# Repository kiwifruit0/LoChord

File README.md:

# LoChord

A real-time MIDI chord controller for **ESP32-P4**, with chord generation, looping, and parameter control. Inspired by the [HiChord](https://hichord.shop/), but not a clone — see `CLAUDE.md` for how the two differ.

LoChord is both a firmware project and a hardware project developed together in one repo.

> **Mid-migration.** The project moved from the ESP32-S3-WROOM-1 to the WT0132P4-A1 (ESP32-P4) module during design. `PINOUT.md` is written against the P4; `firmware/include/config.h` and the KiCad schematic are not yet. See `PINOUT.md`'s "Migration delta" for the work list, and the root `CLAUDE.md` for why the move was made.

## Hardware at a glance

- **WT0132P4-A1-N16R32** module — ESP32-P4, dual-core RISC-V, 16MB flash, 32MB in-package PSRAM, no radio
- 7× Kailh Choc v1 chord switches + 1× loop button, hand-soldered, direct GPIO
- 3× ALPS EC11 clickable rotary encoders (1 UI, 2 control)
- Nintendo Switch joystick module on a 5-pin FPC
- 428×142 2.79" NV3007 TFT LCD, SPI, LVGL UI built in EEZ Studio
- **ES8388** stereo I2S codec with integrated headphone amp, driving a 3.5mm jack
- Native USB, **MIDI only** — recording is via the headphone jack into an audio interface
- 4-pin USB-Serial-JTAG debug header (works concurrently with USB MIDI)

## Repository layout

```
/
├── firmware/     ESP32-P4 PlatformIO project (Arduino framework, via pioarduino)
├── lochord_hw/   KiCad hardware project (schematic + PCB)
└── PINOUT.md     Single source of truth for every pin/net crossing the firmware↔hardware boundary
```

Each directory has its own `CLAUDE.md` with more detail; start with the root `CLAUDE.md` for the full picture.

## Firmware

Built against **`pioarduino/platform-espressif32`**, not the official `platformio/espressif32` platform. The official platform never picked up Arduino-ESP32 3.x (needed for USB MIDI) and has no ESP32-P4 support.

A **custom board JSON is required** — no stock definition matches the N16R32 (16MB flash / 32MB PSRAM) module.

### Development commands

Run from `firmware/`:

Generate `compile_commands.json`:
```
pio run -t compiledb
```

Build and upload:
```
pio run -t upload
```

Serial monitor:
```
pio device monitor
```
Exit with `Ctrl+A` then `Ctrl+X`

Host tests:
```
pio test -e native
```

## Hardware

The schematic (`lochord_hw.kicad_sch`) and PCB (`lochord_hw.kicad_pcb`) live in `lochord_hw/`. After a fresh clone, run:
```
git submodule update --init
```
to pull in the Kailh switch footprint library — without it, KiCad can't resolve the switch footprints.

Note that the switches are **Choc v1** (`PG1350`). Any Choc v2 footprint still present in the schematic is left over from an earlier revision and is wrong.

## Commit convention

Commits are prefixed by which side of the repo they touch:

- `fw:` — firmware-only changes
- `hw:` — hardware-only changes (including schematic/PCB edits)
- `chore:` — repo-wide changes that aren't feature work on either side (restructuring, docs, tooling)
- `fw+hw:` — changes that necessarily touch both sides together (e.g. reassigning a pin)

e.g. `fw: add strum direction toggle`, `hw: swap choc v2 footprints for v1`, `fw+hw: renumber gpio for esp32-p4`.

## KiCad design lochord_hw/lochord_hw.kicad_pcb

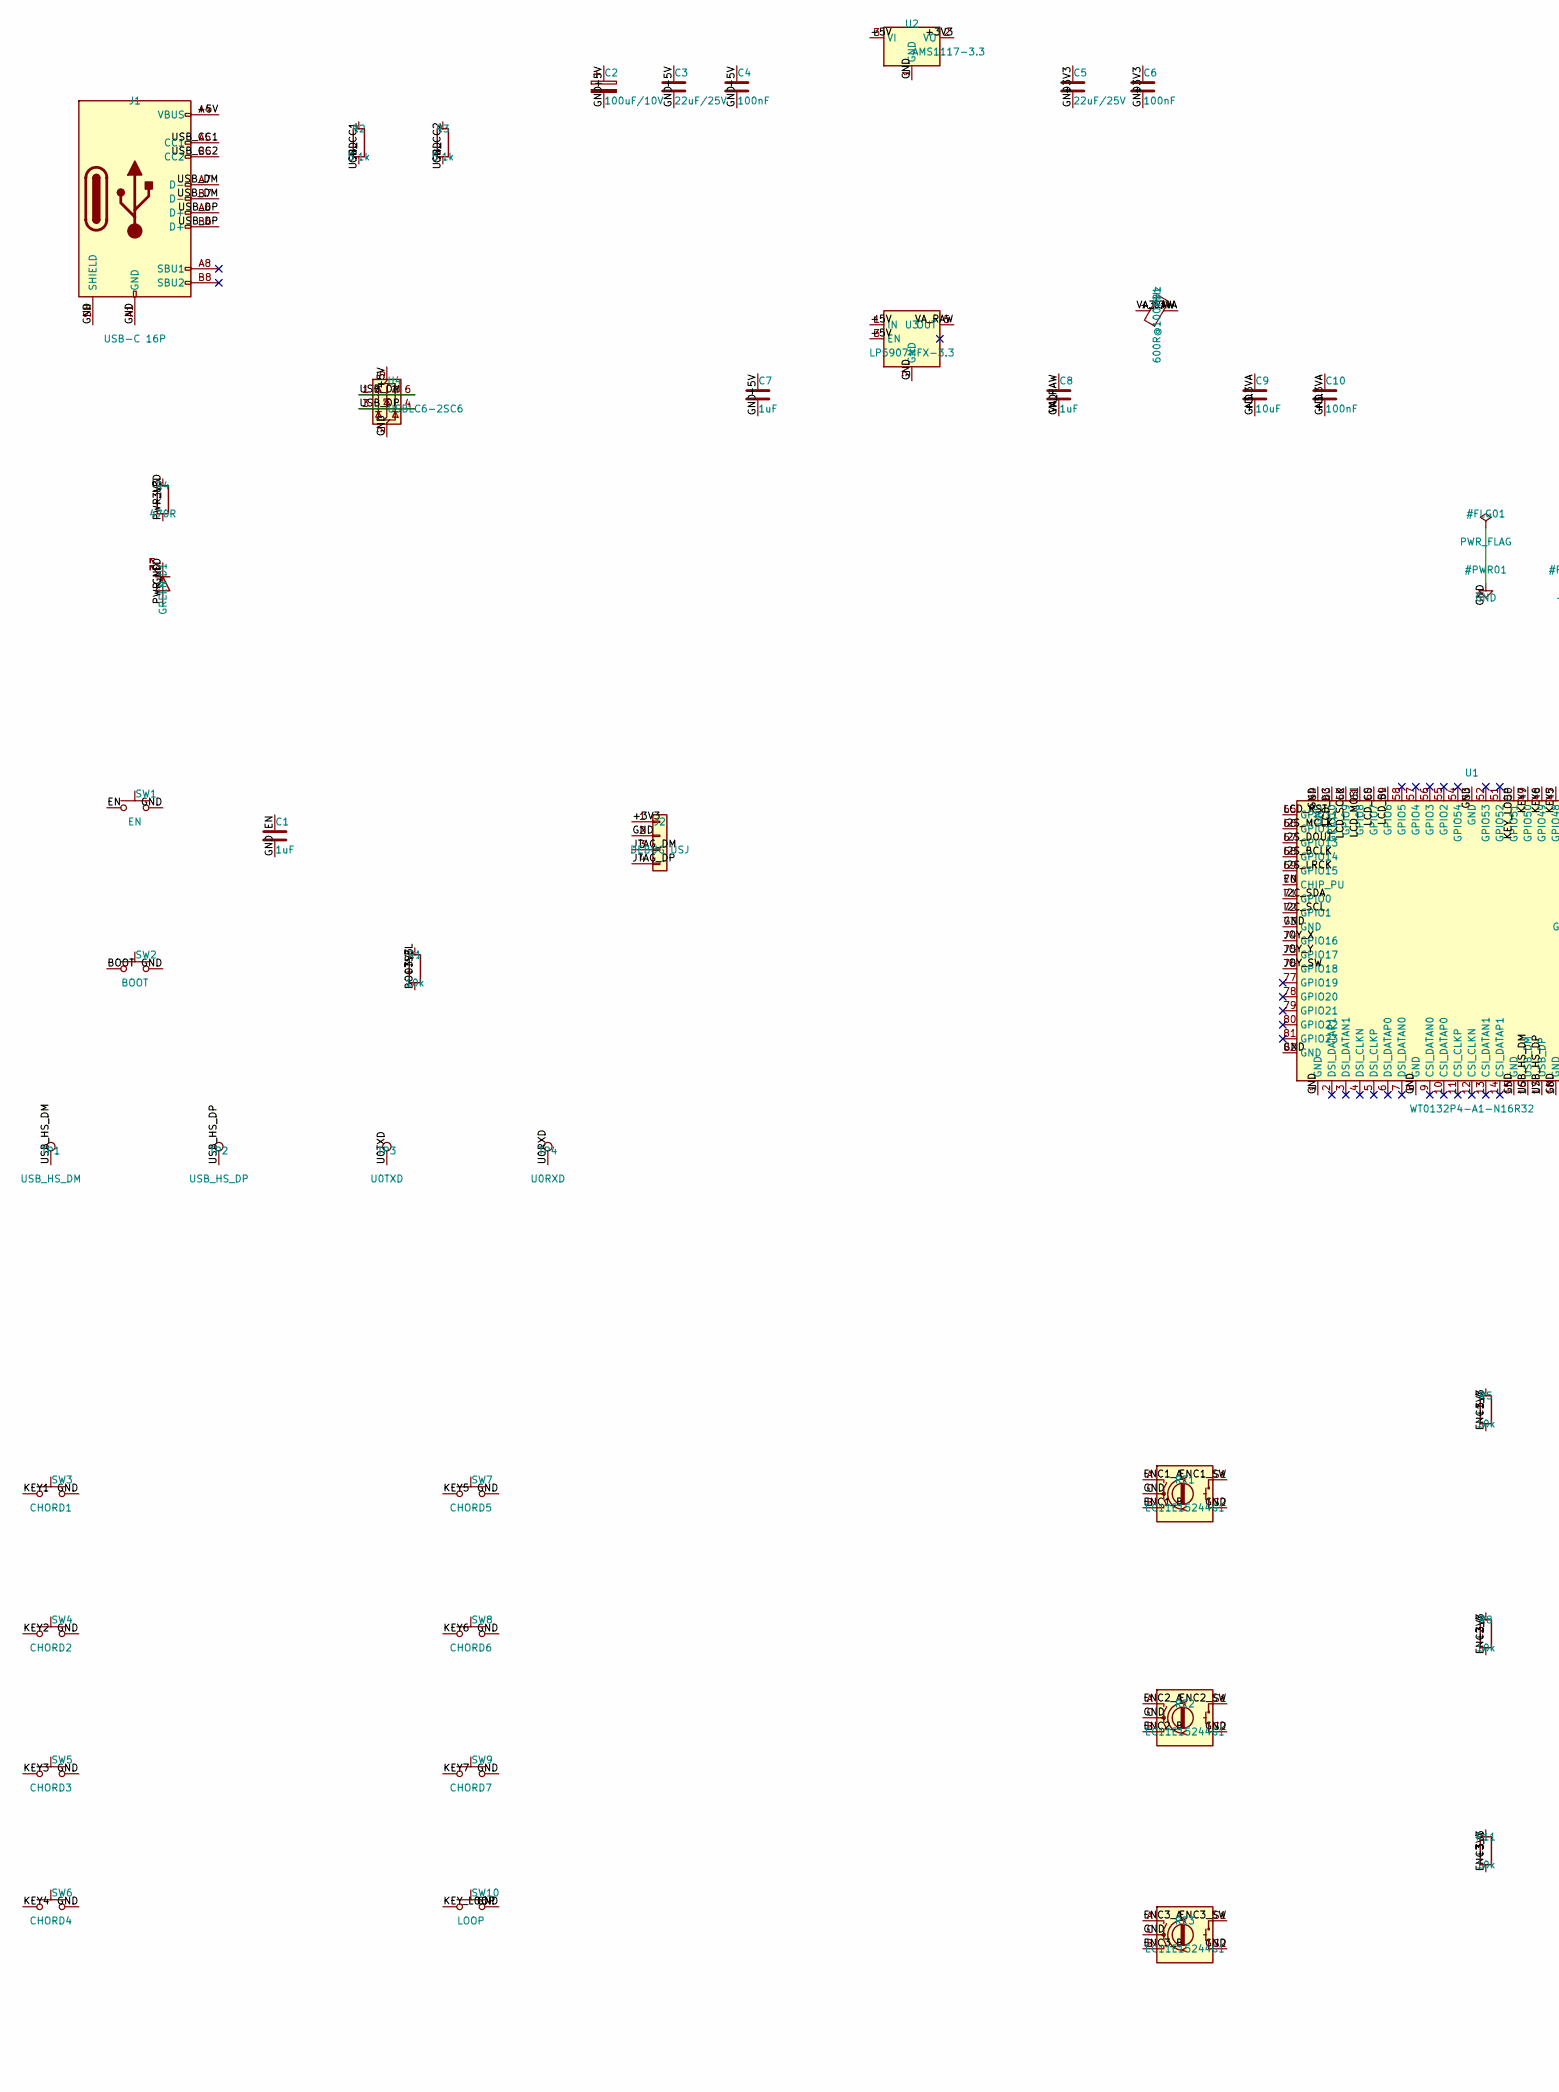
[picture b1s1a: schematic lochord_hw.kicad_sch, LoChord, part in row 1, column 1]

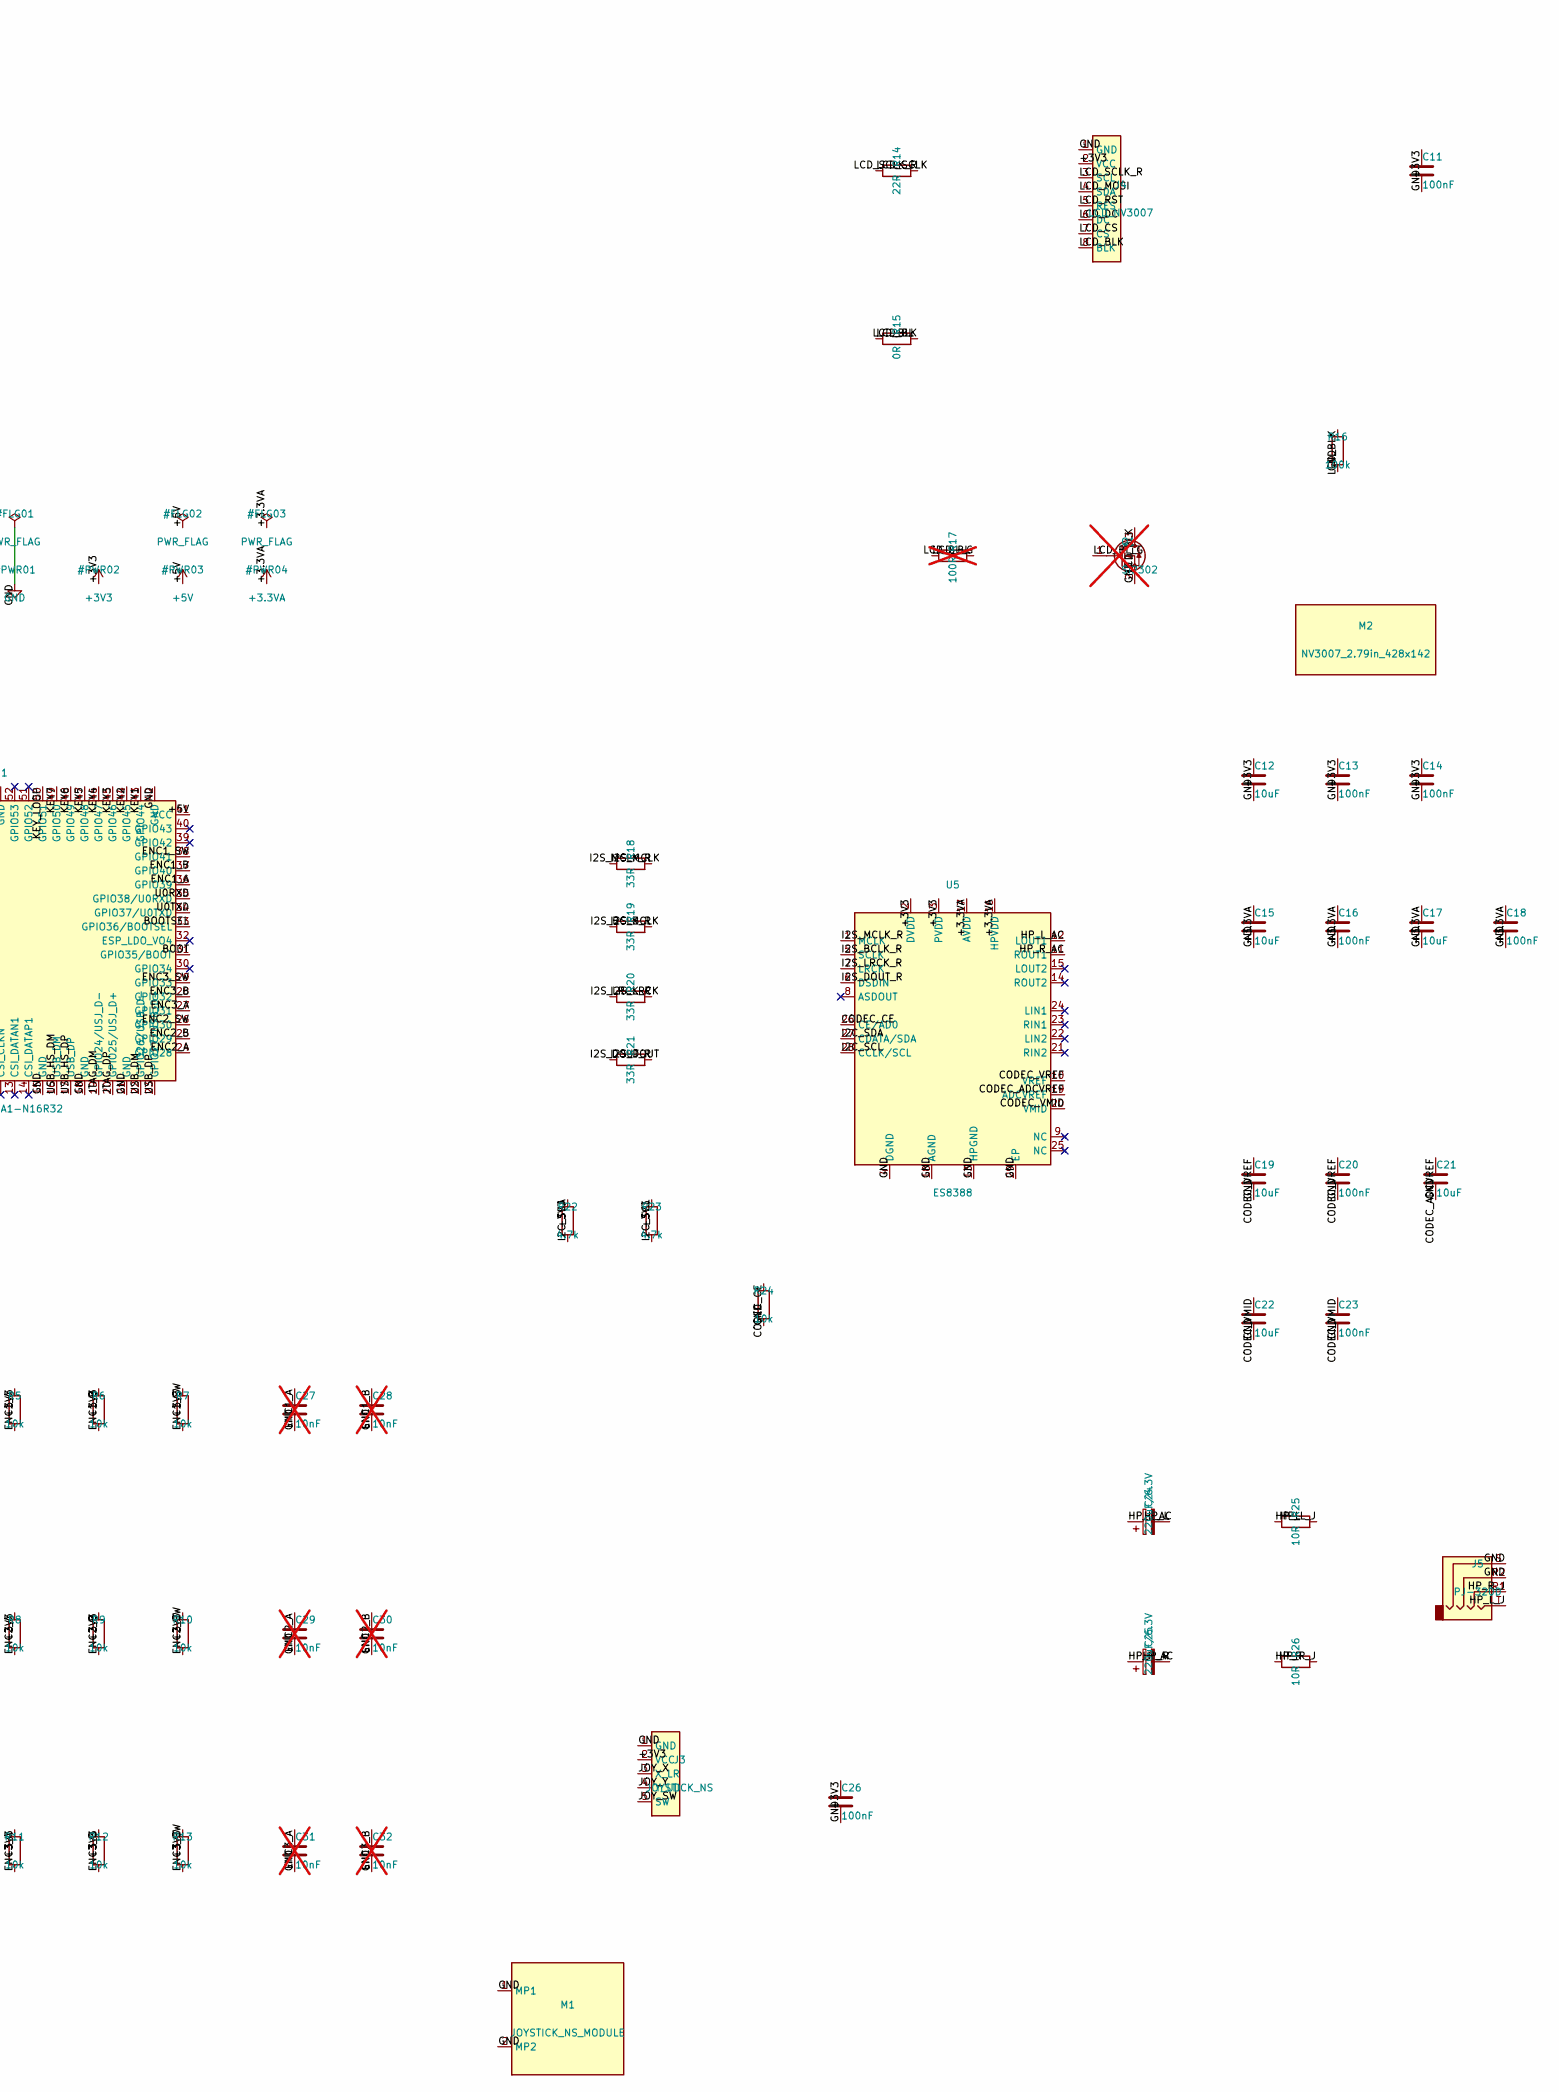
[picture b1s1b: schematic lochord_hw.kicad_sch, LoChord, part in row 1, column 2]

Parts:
C1, C7, C8: 1uF; C_0402_1005Metric; LCSC C52923
C2: 100uF/10V; CP_Elec_5x5.4; LCSC C72473
C3, C5: 22uF/25V; C_0805_2012Metric; LCSC C45783
C4, C6, C10, C11, C13, C14, C16, C18, C20, C23, C26: 100nF; C_0402_1005Metric; LCSC C1525
C9, C12, C15, C17, C19, C21, C22: 10uF; C_0603_1608Metric; LCSC C19702
C24, C25: 220uF/6.3V; CP_Elec_6.3x5.4; LCSC C32514
C27, C28, C29, C30, C31, C32: 10nF; C_0402_1005Metric; LCSC C15195; not fitted
D1: GREEN; LED_0603_1608Metric; LCSC C7496818
FB1: 600R@100MHz; L_0603_1608Metric; LCSC C1002
J1: USB-C 16P; USB_C_Receptacle_HRO_TYPE-C-31-M-12; LCSC C165948
J2: DEBUG USJ; PinHeader_1x04_P2.54mm_Vertical
J3: JOYSTICK_NS; FPC_1x05_P0.50mm_Horizontal_ZIF; LCSC C5213728
J4: LCD_NV3007; FPC_1x08_P0.50mm_Horizontal_ZIF; LCSC C597995
J5: PJ-320D; Jack_3.5mm_PJ320D_Horizontal; LCSC C431535
M1: JOYSTICK_NS_MODULE; Joystick_NintendoSwitch_Module
M2: NV3007_2.79in_428x142; Display_NV3007_2.79in_428x142
Q1: SI2302; SOT-23; LCSC C5296725; not fitted
R1, R5, R6, R7, R8, R9, R10, R11, R12, R13, R24: 10k; R_0402_1005Metric; LCSC C25744
R2, R3: 5.1k; R_0402_1005Metric; LCSC C25905
R4: 470R; R_0402_1005Metric; LCSC C25117
R14: 22R; R_0402_1005Metric; LCSC C25092
R15: 0R; R_0402_1005Metric; LCSC C17168
R16: 100k; R_0402_1005Metric; LCSC C25741
R17: 100R; R_0402_1005Metric; LCSC C25076; not fitted
R18, R19, R20, R21: 33R; R_0402_1005Metric; LCSC C25105
R22, R23: 4.7k; R_0402_1005Metric; LCSC C25900
R25, R26: 10R; R_0402_1005Metric; LCSC C25077
RE1, RE2, RE3: EC11E15244G1; RotaryEncoder_Alps_EC11E-Switch_Vertical_H20mm_CircularMoun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; LCSC C370970
SW1: EN; SW_SMD_TS-1088-AR02016_3.9x3.0mm; LCSC C720477
SW2: BOOT; SW_SMD_TS-1088-AR02016_3.9x3.0mm; LCSC C720477
SW3: CHORD1; SW_Kailh_Choc_V1_2.00u
SW4: CHORD2; SW_Kailh_Choc_V1_2.00u
SW5: CHORD3; SW_Kailh_Choc_V1_2.00u
SW6: CHORD4; SW_Kailh_Choc_V1_2.00u
SW7: CHORD5; SW_Kailh_Choc_V1_1.50u
SW8: CHORD6; SW_Kailh_Choc_V1_1.00u
SW9: CHORD7; SW_Kailh_Choc_V1_1.50u
SW10: LOOP; SW_Kailh_Choc_V1_1.00u
TP1: USB_HS_DM; TestPoint_Pad_D1.5mm
TP2: USB_HS_DP; TestPoint_Pad_D1.5mm
TP3: U0TXD; TestPoint_Pad_D1.5mm
TP4: U0RXD; TestPoint_Pad_D1.5mm
U1: WT0132P4-A1-N16R32; WT0132P4-A1; LCSC TBD
U2: AMS1117-3.3; SOT-223-3_TabPin2; LCSC C6186
U3: LP5907MFX-3.3; SOT-23-5; LCSC C5370990
U4: USBLC6-2SC6; SOT-23-6; LCSC C2687116
U5: ES8388; QFN-28-1EP_4x4mm_P0.45mm_EP2.6x2.6mm_ThermalVias; LCSC C365736

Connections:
+3.3VA: C9.1, C10.1, C15.1, C16.1, C17.1, C18.1, FB1.2, U5.16 (HPVDD), U5.17 (AVDD)
+3V3: C5.1, C6.1, C11.1, C12.1, C13.1, C14.1, C26.1, J2.1, J3.2 (VCC), J4.2 (VCC), R1.1, R4.1, R5.1, R6.1, R7.1, R8.1, R9.1, R10.1, R11.1, R12.1, R13.1, R22.1, R23.1, U2.2 (VO), U5.2 (DVDD), U5.3 (PVDD)
+5V: C2.1, C3.1, C4.1, C7.1, J1.A4 (VBUS), J1.A9 (VBUS), J1.B4 (VBUS), J1.B9 (VBUS), U1.41 (VCC), U2.3 (VI), U3.1 (IN), U3.3 (EN), U4.5 (VBUS)
/BOOT: SW2.1, U1.31 (GPIO35/BOOT)
/BOOTSEL: R1.2, U1.33 (GPIO36/BOOTSEL)
/CODEC_ADCVREF: C21.1, U5.19 (ADCVREF)
/CODEC_CE: R24.1, U5.26 (CE/AD0)
/CODEC_VMID: C22.1, C23.1, U5.20 (VMID)
/CODEC_VREF: C19.1, C20.1, U5.10 (VREF)
/EN: C1.1, SW1.1, U1.70 (CHIP_PU)
/ENC1_A: C27.1, R5.2, RE1.A, U1.36 (GPIO39)
/ENC1_B: C28.1, R6.2, RE1.B, U1.37 (GPIO40)
/ENC1_SW: R7.2, RE1.S1, U1.38 (GPIO41)
/ENC2_A: C29.1, R8.2, RE2.A, U1.24 (GPIO28)
/ENC2_B: C30.1, R9.2, RE2.B, U1.25 (GPIO29)
/ENC2_SW: R10.2, RE2.S1, U1.26 (GPIO30)
/ENC3_A: C31.1, R11.2, RE3.A, U1.27 (GPIO31)
/ENC3_B: C32.1, R12.2, RE3.B, U1.28 (GPIO32)
/ENC3_SW: R13.2, RE3.S1, U1.29 (GPIO33)
/HP_L: C24.2, R25.1
/HP_L_AC: C24.1, U5.12 (LOUT1)
/HP_L_J: J5.T, R25.2
/HP_R: C25.2, R26.1
/HP_R_AC: C25.1, U5.11 (ROUT1)
/HP_R_J: J5.R1, R26.2
/I2C_SCL: R23.2, U1.72 (GPIO1), U5.28 (CCLK/SCL)
/I2C_SDA: R22.2, U1.71 (GPIO0), U5.27 (CDATA/SDA)
/I2S_BCLK: R19.1, U1.68 (GPIO14)
/I2S_BCLK_R: R19.2, U5.5 (SCLK)
/I2S_DOUT: R21.1, U1.67 (GPIO13)
/I2S_DOUT_R: R21.2, U5.6 (DSDIN)
/I2S_LRCK: R20.1, U1.69 (GPIO15)
/I2S_LRCK_R: R20.2, U5.7 (LRCK)
/I2S_MCLK: R18.1, U1.66 (GPIO12)
/I2S_MCLK_R: R18.2, U5.1 (MCLK)
/JOY_SW: J3.5 (SW), U1.76 (GPIO18)
/JOY_X: J3.3 (X_LR), U1.74 (GPIO16)
/JOY_Y: J3.4 (Y_UD), U1.75 (GPIO17)
/JTAG_DM: J2.3, U1.19 (GPIO24/USJ_D-)
/JTAG_DP: J2.4, U1.20 (GPIO25/USJ_D+)
/KEY1: SW3.1, U1.43 (GPIO44)
/KEY2: SW4.1, U1.44 (GPIO45)
/KEY3: SW5.1, U1.45 (GPIO46)
/KEY4: SW6.1, U1.46 (GPIO47)
/KEY5: SW7.1, U1.47 (GPIO48)
/KEY6: SW8.1, U1.48 (GPIO49)
/KEY7: SW9.1, U1.49 (GPIO50)
/KEY_LOOP: SW10.1, U1.50 (GPIO51)
/LCD_BL: R15.1, R17.1, U1.59 (GPIO6)
/LCD_BLK: J4.8 (BLK), Q1.3 (D), R15.2, R16.1
/LCD_BL_G: Q1.1 (G), R17.2
/LCD_CS: J4.7 (CS), U1.60 (GPIO7)
/LCD_DC: J4.6 (DC), U1.63 (GPIO10)
/LCD_MOSI: J4.4 (SDA), U1.61 (GPIO8)
/LCD_RST: J4.5 (RES), U1.65 (GPIO11)
/LCD_SCLK: R14.1, U1.62 (GPIO9)
/LCD_SCLK_R: J4.3 (SCL), R14.2
/PWR_LED: D1.2 (A), R4.2
/U0RXD: TP4.1, U1.35 (GPIO38/U0RXD)
/U0TXD: TP3.1, U1.34 (GPIO37/U0TXD)
/USB_CC1: J1.A5 (CC1), R2.1
/USB_CC2: J1.B5 (CC2), R3.1
/USB_DM: J1.A7 (D-), J1.B7 (D-), U1.22 (GPIO26/USB_D-), U4.1 (I/O1), U4.6 (I/O1)
/USB_DP: J1.A6 (D+), J1.B6 (D+), U1.23 (GPIO27/USB_D+), U4.3 (I/O2), U4.4 (I/O2)
/USB_HS_DM: TP1.1, U1.16 (USB_DM)
/USB_HS_DP: TP2.1, U1.17 (USB_DP)
/VA_RAW: C8.1, FB1.1, U3.5 (OUT)
GND: C1.2, C2.2, C3.2, C4.2, C5.2, C6.2, C7.2, C8.2, C9.2, C10.2, C11.2, C12.2, C13.2, C14.2, C15.2, C16.2, C17.2, C18.2, C19.2, C20.2, C21.2, C22.2, C23.2, C26.2, C27.2, C28.2, C29.2, C30.2, C31.2, C32.2, D1.1 (K), J1.A1 (GND), J1.A12 (GND), J1.B1 (GND), J1.B12 (GND), J1.SH (SHIELD), J2.2, J3.1 (GND), J4.1 (GND), J5.R2, J5.S, M1.1 (MP1), M1.2 (MP2), Q1.2 (S), R2.2, R3.2, R16.2, R24.2, RE1.C, RE1.S2, RE2.C, RE2.S2, RE3.C, RE3.S2, SW1.2, SW2.2, SW3.2, SW4.2, SW5.2, SW6.2, SW7.2, SW8.2, SW9.2, SW10.2, U1.1 (GND), U1.8 (GND), U1.15 (GND), U1.18 (GND), U1.21 (GND), U1.42 (GND), U1.53 (GND), U1.64 (GND), U1.73 (GND), U1.82 (GND), U2.1 (GND), U3.2 (GND), U4.2 (GND), U5.4 (DGND), U5.13 (HPGND), U5.18 (AGND), U5.29 (EP)

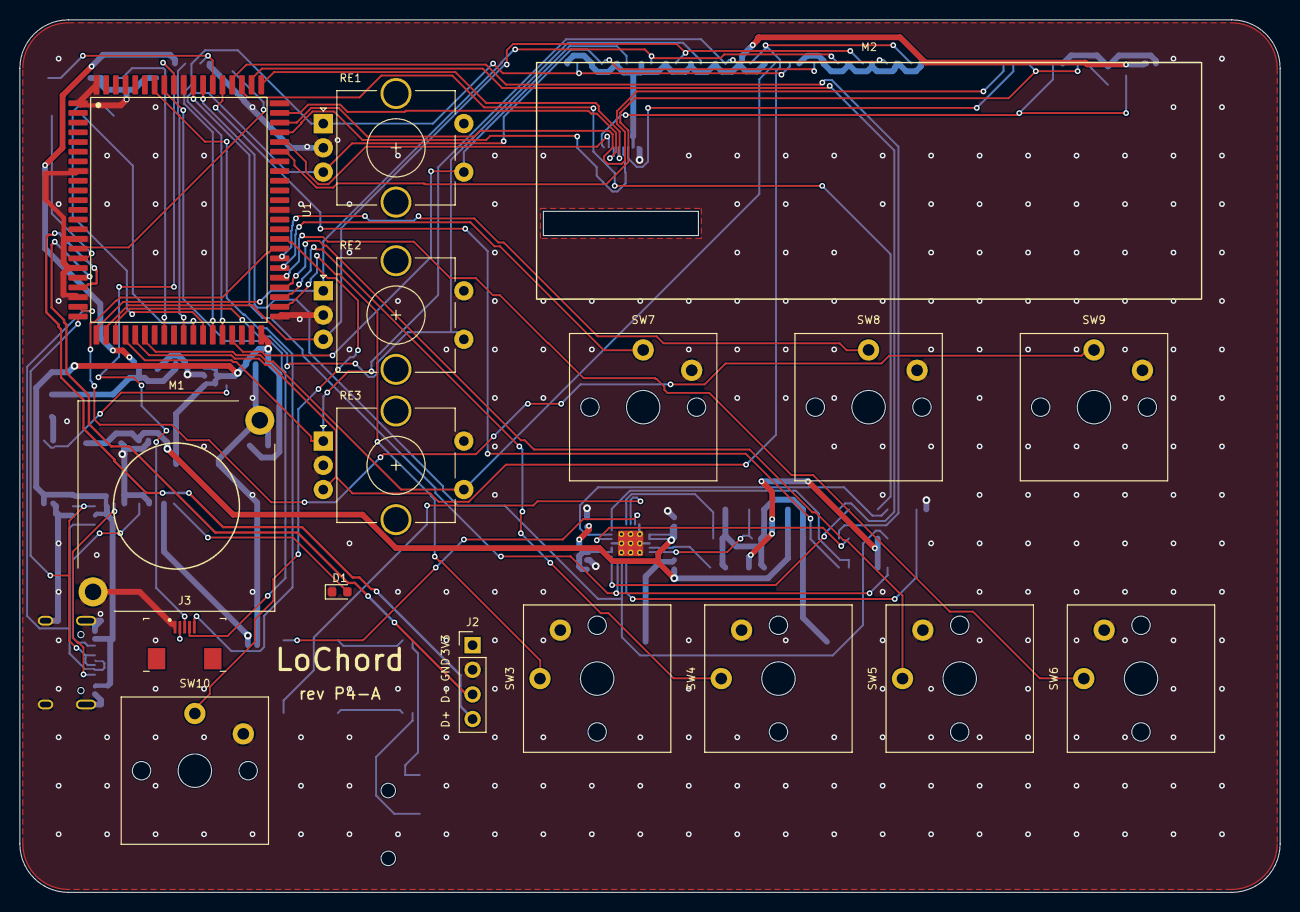
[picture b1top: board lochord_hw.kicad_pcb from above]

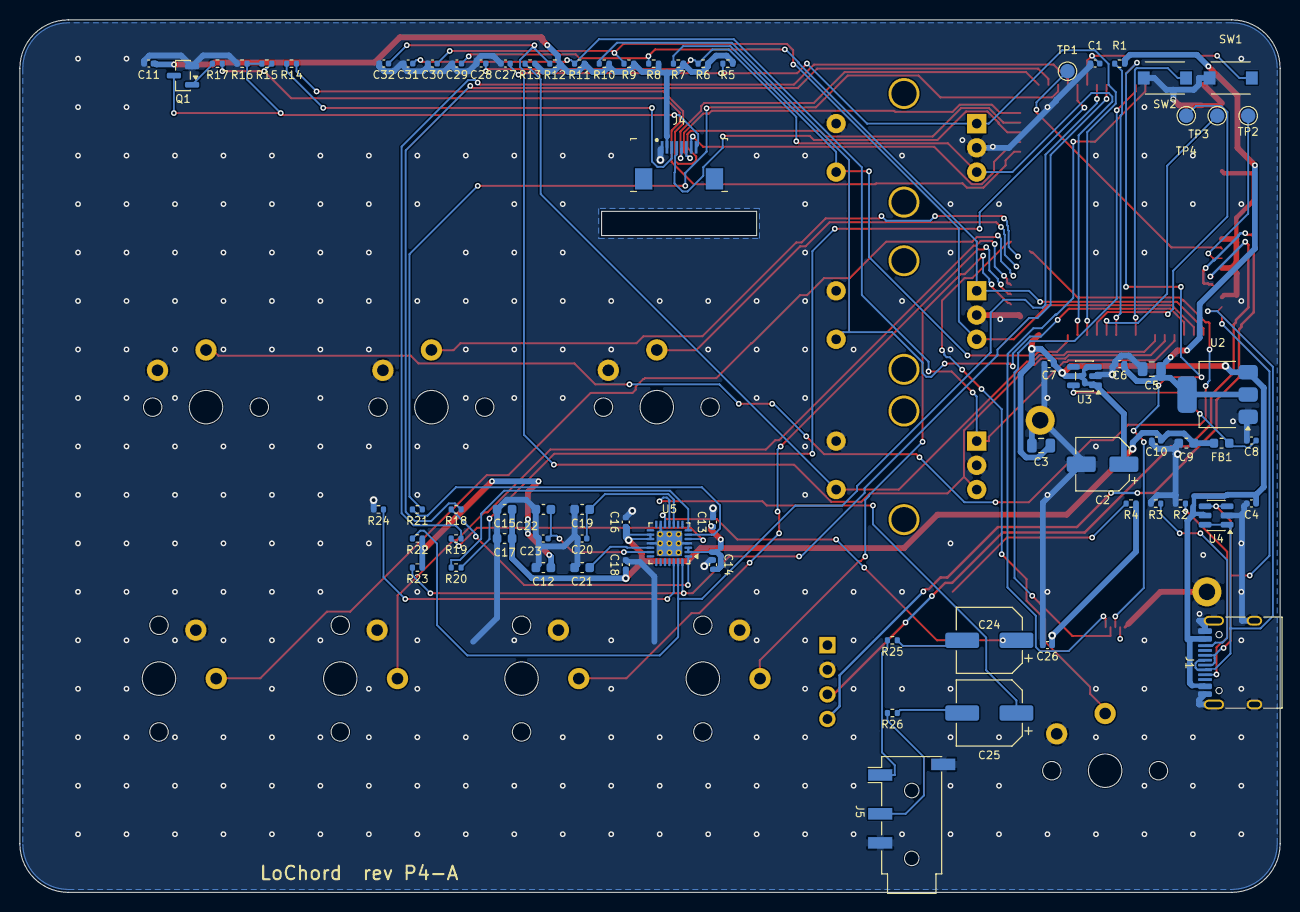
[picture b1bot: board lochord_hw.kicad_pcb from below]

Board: 4 copper layers, 130.0 x 90.0 mm, 90 parts (73 on the bottom side), 68 nets.

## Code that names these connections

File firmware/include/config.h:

#pragma once

#include <cstdint>

// See ../PINOUT.md — it is the source of truth. If this file and PINOUT.md
// disagree, this file is wrong.
//
// Target module: ESP32-S3-WROOM-1 N8R2 (quad PSRAM). Chord buttons 1-3 sit on
// GPIO35/36/37, which an octal-PSRAM module (N8R8/N16R8) uses internally.

// buttons
#define NUM_BUTTONS 7

// index order matches physical position: bottom row left->right, then top row
const uint8_t buttonPins[NUM_BUTTONS] = {35, 36, 37, 38, 39, 40, 41};

#define PIN_BUTTON_LOOP 46

// encoders
#define PIN_ENCODER_UI_A 21
#define PIN_ENCODER_UI_B 47
#define PIN_ENCODER_UI_SW 48

#define PIN_ENCODER_CTRL1_A 7
#define PIN_ENCODER_CTRL1_B 15
#define PIN_ENCODER_CTRL1_SW 16

#define PIN_ENCODER_CTRL2_A 17
#define PIN_ENCODER_CTRL2_B 18
#define PIN_ENCODER_CTRL2_SW 8

// joystick — both axes on ADC1, which stays usable with the radio enabled
#define PIN_JOYSTICK_LR 4  // ADC1_CH3
#define PIN_JOYSTICK_UD 5  // ADC1_CH4
#define PIN_JOYSTICK_BUTTON 6

// display — CS/MOSI/SCK are SPI2's IO_MUX pins, not routed via the GPIO matrix
#define PIN_LCD_BL 9
#define PIN_LCD_CS 10
#define PIN_LCD_MOSI 11
#define PIN_LCD_SCK 12
#define PIN_LCD_DC 13
#define PIN_LCD_RST 14
#define PIN_LCD_MISO -1
#define LCD_SPI_HZ 40000000

// audio — reserved for the future I2S DAC, not wired yet. See ../PINOUT.md
#define PIN_I2S_DOUT 42
#define PIN_I2S_BCLK 2
#define PIN_I2S_WS 1

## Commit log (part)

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2026-03-23 logic for buttons
2026-03-24 usb serial working
2026-03-24 updated gitignore
2026-03-25 can send midi notes
2026-03-25 buttons send midi notes
2026-03-27 added chordGenerator and basic theory
2026-03-27 refactored
2026-03-27 tests for chordgen
2026-03-28 added chord intervals
2026-03-28 added note -> chords
2026-03-28 fixed tests
2026-03-28 added MidiController
2026-03-28 structure of midicontroller
2026-03-30 added sendNote and sendChord
2026-03-31 consistent var names
2026-04-03 basic strummer class
2026-04-03 strum working with no setters
2026-04-04 added random strum
2026-04-05 strum working, dom7 still broken
2026-04-05 fixed sus2 + sus4, added serial
2026-04-07 added arp mode, no note off
2026-04-07 added arp note off
2026-04-07 changed noteOff so chords don't interact
2026-05-02 TFT_eSPI setup
2026-05-02 reverted tft
2026-05-03 added basic display module
2026-05-03 modularised lgvl
2026-05-03 changed default font
2026-05-05 basic main ui
2026-05-05 ui for main screen
2026-05-06 theme switcher logic
2026-05-07 buttons change root on ui
2026-05-07 buttons change quality
2026-05-07 fixed note off
2026-05-07 added usb detection to ui
2026-05-08 changed architecture to add kicad hardware directory
2026-05-08 hw: added esp32 footprint
2026-05-10 fw: fixed tests and added joystick positioning
2026-05-10 fw: joystick matrix updates with button press
2026-05-10 fw: rotary encoder button and turn detection
2026-06-04 pcb v2
2026-06-29 removed hw dir from git
2026-06-29 fw: added deadzone and jitter reduce to joystick
